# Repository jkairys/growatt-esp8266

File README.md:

# growatt-esp8266
A library to monitor a Growatt MTL-5000 using an ESP8266 (Wemos D1) via a modbus over RS232 interface.

## Software
The library uses a software serial port to connect to the inverter to retrieve data using its Modbus interface. Modbus provides a set of predefined parameters available at certain addresses, which can be queried using a "read register" commmand. This library will:
* Create a software serial port on the pins you specify
* Create a modbus master using this serial port
* Read data from the modbus client (the inverter) registers, decode it and make it available via the library

### Using the library
```
#include <GrowattInverter.h>
#define PIN_TX D5
#define PIN_RX D6
#define SLAVE_ADDRESS 1
GrowattInverter inverter(PIN_RX, PIN_TX, SLAVE_ADDRESS);

void setup(){
  Serial.begin(9600);
}

void loop(){
  inverter.read();
  if(inverter.valid){
    // Power output from the PV panels
    Serial.println(inverter.Ppv);
    // Power output from the inverter
    Serial.println(inverter.Pac1);
  }else{
    Serial.println("Inverter read failed");
  }
  delay(1000);
}

```

## Hardware
See the `hardware/` directory for EAGLE schematic and circuit board design. 
To simplify board design and fabrication, the board uses a module for the esp8266 and all through hole components beyond this.

The board itself is comprised of:
* Wemos D1 Mini
* LM7805 voltage regulator
* 1x330uF capacitor (for main power)
* MAX232 level converter
* 3x 1uF capacitors (for MAX232)
* 3x 3mm leds + 1/4W resistors (optional)

### Pinout
The growatt inverter I have has a DB9 connector for an RS232 connection, which has the pinout:
```
    FROM INVERTER
-----------------------   2 = TX
\ (5) (4) (3) (2) (1) /   3 = RX
 \  (9) (8) (7) (6)  /    5 = GND
  \_________________/     9 = V+ (about 8 volts)

  Inverter DB9           Our DB9       PCB         Wemos
    (female)              (male)       (J4)        (pins)
       2 ---(TX)----(RX)--- 2 --------- 3 ---(RX)--- D6
       3 ---(RX)----(TX)--- 3 --------- 4 ---(TX)--- D5
       5 ---(GND)---------- 5 --------- 1 ---------- GND
       9 ---(V+)----------- 9 --------- 2 -- VREG -- VCC 

```

## Sample project
I've included a complete sample project using the board and software library if you just want to get this running on your own inverter. It uses an MQTT + WiFi wrapper library I put together a while ago called _iot-thing_ but you should be easily able to rip this out and use your own code for the internet / wifi connectivity side of things.

## Enclosure
Coming soon...

## Todo
* Example project should use self configuring captive portal for wifi setup
* Add a simple web UI to show present values from the inverter
* WiFi Serial debugging using socket

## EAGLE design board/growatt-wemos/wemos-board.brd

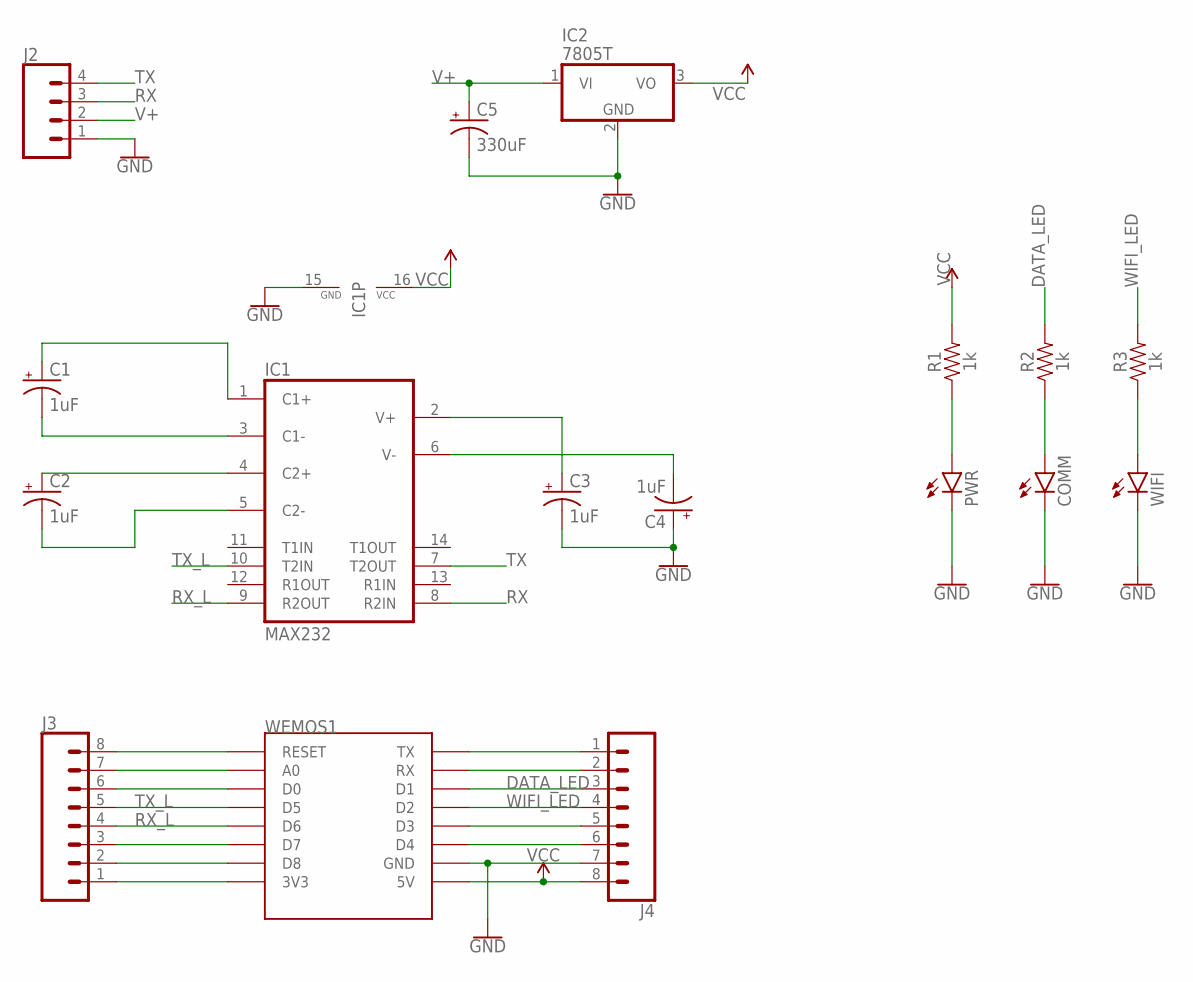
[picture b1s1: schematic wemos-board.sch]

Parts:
C1, C2, C3, C4: 1uF; CPOL-RADIAL-2.5MM-6.5MM
C5: 330uF; CPOL-RADIAL-2.5MM-6.5MM
COMM: LED3MM
IC1: MAX232; DIL16
IC2: 7805T; TO220H
J2: CONN_04; 1X04
J3, J4: CONN_08"; 1X08
PWR: LED3MM
R1, R2, R3: 1k; AXIAL-0.3-KIT
WEMOS1: WEMOS-D1-MINI
WIFI: LED3MM

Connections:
DATA_LED: J4.3, R2.P$2 (2), WEMOS1.D1
GND: C3.2 (-), C4.1 (+), C5.2 (-), COMM.K (C), IC1.15 (GND), IC2.2 (GND), J2.1, J4.7, PWR.K (C), WEMOS1.GND, WIFI.K (C)
unnamed: C1.1 (+), IC1.1 (C1+)
unnamed: C1.2 (-), IC1.3 (C1-)
unnamed: C2.1 (+), IC1.4 (C2+)
unnamed: C2.2 (-), IC1.5 (C2-)
unnamed: C3.1 (+), IC1.2 (V+)
unnamed: C4.2 (-), IC1.6 (V-)
unnamed: J3.8, WEMOS1.RESET
unnamed: J3.7, WEMOS1.A0
unnamed: J3.6, WEMOS1.D0
unnamed: J3.3, WEMOS1.D7
unnamed: J3.2, WEMOS1.D8
unnamed: J3.1, WEMOS1.3V3
unnamed: J4.1, WEMOS1.TX
unnamed: J4.2, WEMOS1.RX
unnamed: J4.5, WEMOS1.D3
unnamed: J4.6, WEMOS1.D4
unnamed: PWR.A, R1.P$1 (1)
unnamed: COMM.A, R2.P$1 (1)
unnamed: R3.P$1 (1), WIFI.A
RX: IC1.8 (R2IN), J2.3
RX_L: IC1.9 (R2OUT), J3.4, WEMOS1.D6
TX: IC1.7 (T2OUT), J2.4
TX_L: IC1.10 (T2IN), J3.5, WEMOS1.D5
V+: C5.1 (+), IC2.1 (VI), J2.2
VCC: IC1.16 (VCC), IC2.3 (VO), J4.8, R1.P$2 (2), WEMOS1.5V
WIFI_LED: J4.4, R3.P$2 (2), WEMOS1.D2

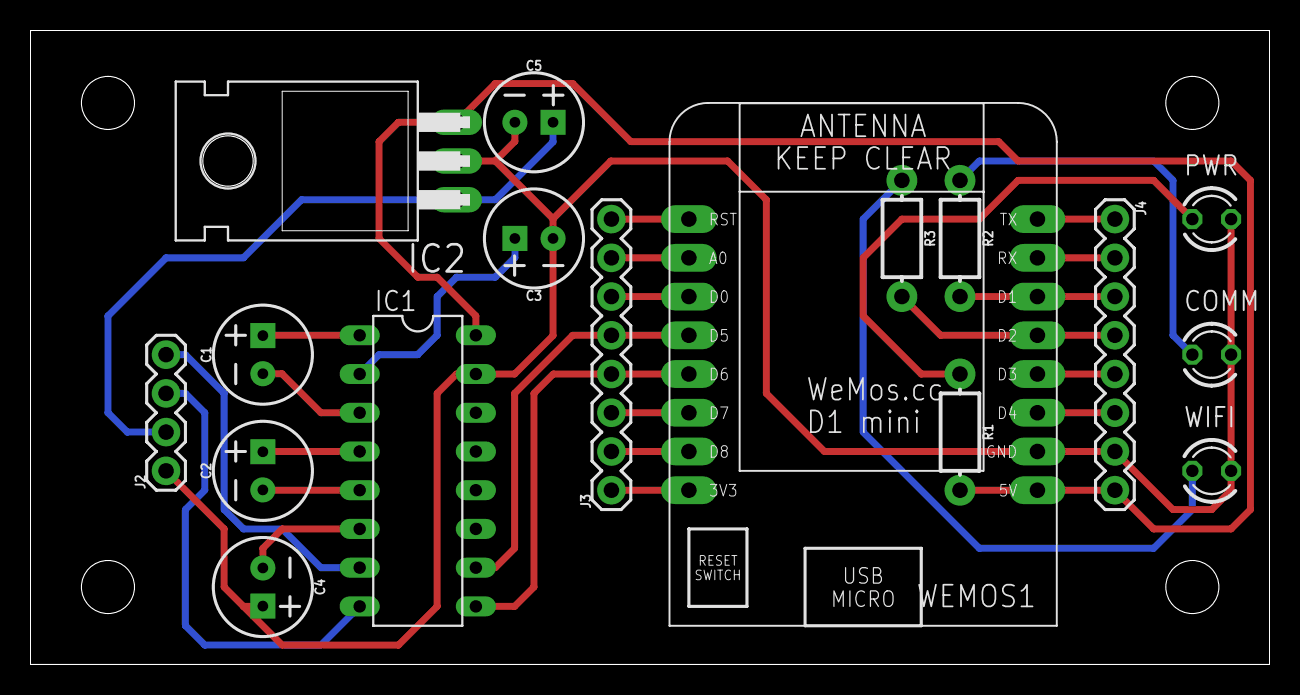
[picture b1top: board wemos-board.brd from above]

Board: 2 copper layers, 81.3 x 41.6 mm, 17 parts (0 on the bottom side), 28 nets.

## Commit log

2016-09-18 Growatt Modbus to MQTT bridge
2016-09-18 Provide inverter status
2020-02-09 adding vendor docs
2020-02-29 updated to use GrowattInverter library
2020-02-29 restructuring repo to work with platform io library management
2020-02-29 removing .vscode library
2020-02-29 removed settings from version control
2020-02-29 remove included settings file since it is not in git now

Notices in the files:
parts and their libraries:
SparkFun-Capacitors: Licensing: Creative Commons ShareAlike 4.0 International - https://creativecommons.org/licenses/by-sa/4.0
